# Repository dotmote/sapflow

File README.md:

# Sapflow Using the External Heat Ratio Method

So you want to measure sapflow in plants? You and me both, buddy. The goal of this project is to create an open-source, accurate, robust, low-cost, and low-power system to help answer the age-old question: "How is my plant doing?"

## Getting Started
Take a look at the hardware and software sections below for instructions on what you'll need to set up your own system and join in on improving the project.

## Hardware

### Sapflow Gauge
First, you'll need a way to measure and record the temperature at two specific points (equidistant from a central heating element) along the stem of your plant:

To build the gauge, you'll need: (1) the PCB; and (2) the components.

#### Fabricate the PCB
See here for the [KiCad PCB files](/hardware/sapflow_gauge/kicad/sapflow_gauge). Follow the directions from your favorite PCB fabrication service (e.g., OSHPark, JLCPCB, Seeed Studio, etc.), and order your desired quantity of PCBs.

#### Gather the Parts
See here for the [parts list](/hardware/sapflow_gauge/sapflow_gauge_parts.md). Go to your favorite electronic components distributor (e.g., Digikey, Arrow, Mouser, etc.) and order your desired quantity of components.

### Microcontroller
Second, you'll need a microcontroller that has an available GPIO pin (3.3V to 5V) and can communicate via I2C. We've found the ESP32 (specifically, the [LOLIN D32 Pro](https://www.aliexpress.com/item/32883116057.html) dev board) to be great for rapid prototyping with its relatively large onboard RAM, built-in WiFi, and low cost. For field experiments, it might make more sense to use a board with more low-power optimizations.

#### Microcontroller Shield
To reduce wiring, you might want to use a shield to interface your microcontroller with the sapflow gauge connector. See [here](/hardware/microcontroller_shield/d32_pro/d32_shield.md) for our shield design for the D32 Pro.

## Software

### Microcontroller Firmware
You'll need software running on your microcontroller to read data from the connected sapflow gauge. See [here](/software/microcontroller/d32_pro) for the Arduino code we used for the D32 Pro.

### Edge Compute Node
If you're using microcontrollers with WiFi connectivity, it's very convenient to have all of the data streaming into a single place. We like using a Raspberry Pi as an [MQTT](https://mosquitto.org/) broker, collecting data points from all of the networked sensor devices. See [here](/software/edge_compute_node/raspberry_pi) for more info.

## Data Visualization

Visualize your hard-earned data with this [Observable notebook](https://observablehq.com/d/a2d68ed97662840b).

Raw data:

After processing:

## References
We've stood on the shoulders of countless giants in working on this project. Below is a non-exhaustive list of the many previous efforts that we drew heavily from (let us know who we've missed and we'll make sure to add them):

### Sapflow
- Burgess, S.S.O., Adams, M.A., Turner, N.C., Beverly, C.R., Ong, C.K., Khan, A.A.H., and Bleby, T.M. (2001). An improved heat pulse method to measure low and reverse rates of sap flow in woody plants. Tree Physiology 21, 589–598. 
- Clearwater, M.J., Luo, Z., Mazzeo, M., and Dichio, B. (2009). An external heat pulse method for measurement of sap flow through fruit pedicels, leaf petioles and other small-diameter stems. Plant, Cell & Environment 32, 1652–1663.
- Marshall, D.C. (1958). Measurement of Sap Flow in Conifers by Heat Transport. Plant Physiol. 33, 385–396.
- Skelton, R. (2017). Miniature External Sapflow Gauges and the Heat Ratio Method for Quantifying Plant Water Loss. BIO-PROTOCOL 7.

### Open-Source Research Tools
- Chris Lucani & Team @ Brodribb Lab, University of Tasmania: [Open Source OV](http://www.opensourceov.org/).
- OPEnS Lab, Oregon State University: [Sap Flow Meter](https://github.com/OPEnSLab-OSU/OPEnS-Lab-Home/wiki/Sap-Flow-Meter).

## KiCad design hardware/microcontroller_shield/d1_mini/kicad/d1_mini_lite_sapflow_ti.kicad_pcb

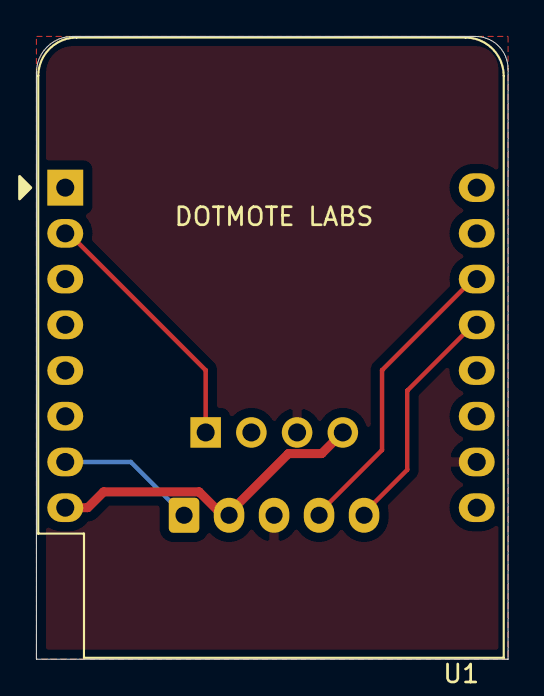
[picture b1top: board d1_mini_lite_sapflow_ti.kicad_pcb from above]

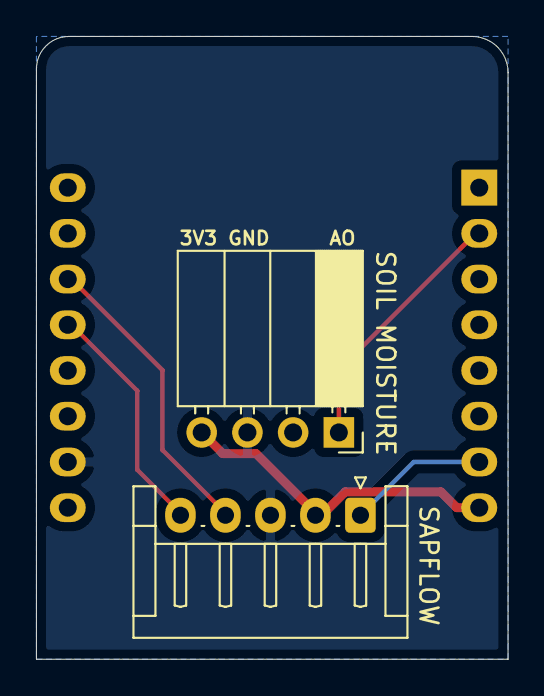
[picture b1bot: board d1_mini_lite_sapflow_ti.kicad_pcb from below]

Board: 2 copper layers, 26.2 x 34.6 mm, 3 parts (2 on the bottom side), 6 nets.

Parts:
SAPFLOW: sapflow_gauge_5_pin; JST_EH_S5B-EH_1x05_P2.50mm_Horizontal
SOIL MOISTURE: soil_moisture_4_pin; PinSocket_1x04_P2.54mm_Horizontal
U1: WeMos_D1_mini; WEMOS_D1_mini_light

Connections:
+3V3: SAPFLOW.2, SOIL MOISTURE.4, U1.8
GND: SAPFLOW.3, SOIL MOISTURE.3, U1.10
unnamed: SOIL MOISTURE.1, U1.2
unnamed: SAPFLOW.1, U1.7
unnamed: SAPFLOW.5, U1.13
unnamed: SAPFLOW.4, U1.14

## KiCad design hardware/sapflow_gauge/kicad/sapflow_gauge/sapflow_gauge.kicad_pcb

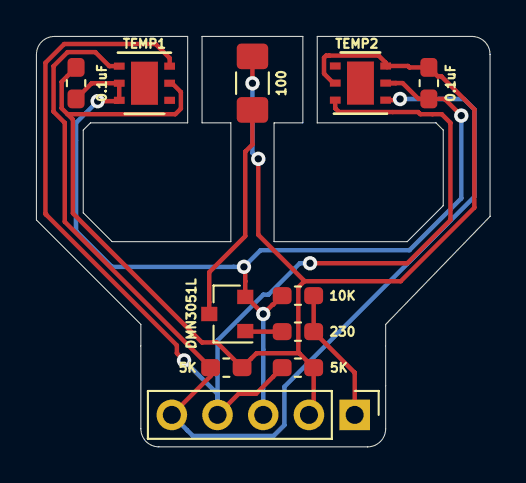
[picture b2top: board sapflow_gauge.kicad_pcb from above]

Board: 2 copper layers, 25.2 x 22.8 mm, 11 parts (0 on the bottom side), 7 nets.

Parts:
0.1uF, 0.1uF#2: 0.1uF; C_0603_1608Metric_Pad1.05x0.95mm_HandSolder
5K, 5K#2: 5K; R_0603_1608Metric_Pad1.05x0.95mm_HandSolder
10K: 10K; R_0603_1608Metric_Pad1.05x0.95mm_HandSolder
100: 100; R_1206_3216Metric_Pad1.42x1.75mm_HandSolder
230: 230; R_0603_1608Metric_Pad1.05x0.95mm_HandSolder
 : Conn_01x05_Female; PinHeader_1x05_P2.54mm_Vertical
DMN3051L: DMN3051L; SOT-23
TEMP1, TEMP2: HDC2080; Texas_PWSON-N6

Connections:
+3V3: 0.1uF.1, 0.1uF#2.1, 5K.1, 5K#2.1, 100.2, .2, TEMP1.5, TEMP2.3, TEMP2.5
GND: 0.1uF.2, 0.1uF#2.2, 10K.1, .3, DMN3051L.2, TEMP1.2, TEMP1.3, TEMP2.2
unnamed: 10K.2, 230.1, .1
unnamed: 5K.2, .4, TEMP1.6, TEMP2.6
unnamed: 5K#2.2, .5, TEMP1.1, TEMP2.1
unnamed: 230.2, DMN3051L.1
unnamed: 100.1, DMN3051L.3

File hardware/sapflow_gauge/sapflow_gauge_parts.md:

# Sapflow Gauge Parts

![sapflow gauge 3d](/docs/sapflow_gauge_3d.png)

In order to use the gauge, you'll need to:
1. Build the gauge head; and
2. Connect the gauge head to your microcontroller.

## Gauge Head Parts

Digikey links provided for convenience, but feel free to order from your favorite electronic components distributor.
| Part | Link | Quantity Needed Per Gauge |
|----------------------------------|------------------------------------------------------------------------------------------------------------------|---------------------------|
| HDC2080 Temperature & Humidity Sensor (6-WSON Package) | https://www.digikey.com/product-detail/en/texas-instruments/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 | 2 |
| DMN3051L-7 Logic Level Mosfet (SOT23 Package) | https://www.digikey.com/product-detail/en/diodes-incorporate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 | 1 |
| 100 Ohm Resistor (1206 Package) | https://www.digikey.com/product-detail/en/stackpole-electron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 | 1 |
| 270 Ohm Resistor (0603 Package) | https://www.digikey.com/product-detail/en/panasonic-electron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 | 1 |
| 5K Ohm Resistor (0603 Package) | https://www.digikey.com/product-detail/en/te-connectivity-pa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 | 2 |
| 10K Ohm Resistor (0603 Package) | https://www.digikey.com/product-detail/en/stackpole-electron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 | 1 |
| 0.1 uF Capacitor (0603 Package) | https://www.digikey.com/product-detail/en/samsung-electro-me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 | 2 |

## Gauge Head Connector Parts
You can use any method you'd like to connect the 5 pins (HEAT, 3V3, GND, SCL, SDA) from the gauge head to your microcontroller. We've had good results using RJ11 connectors with CAT3 ethernet cables up to ~10 feet (~3 meters).

| Part | Link |
|-----------------------|-------------------------------------------------------------------------------------------------|
| RJ11 Breakout Board | https://www.digikey.com/product-detail/en/sparkfun-electroni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 |
| RJ11 Female Connector | https://www.digikey.com/product-detail/en/amphenol-icc-fci/5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 |

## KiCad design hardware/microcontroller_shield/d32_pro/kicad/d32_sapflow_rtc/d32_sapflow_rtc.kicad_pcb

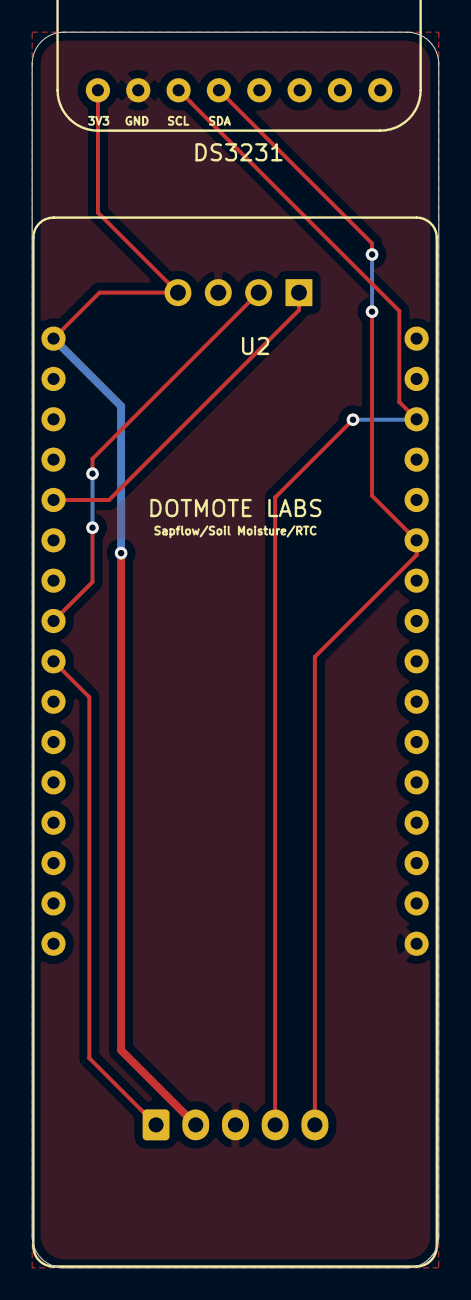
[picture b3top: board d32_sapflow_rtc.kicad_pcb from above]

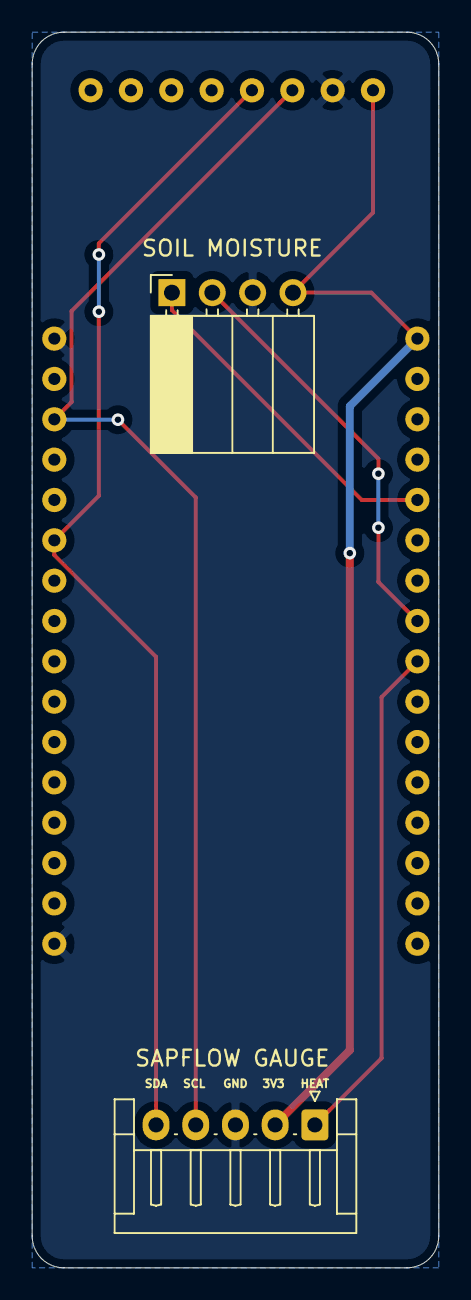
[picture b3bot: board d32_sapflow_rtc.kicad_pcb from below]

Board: 2 copper layers, 25.6 x 77.8 mm, 4 parts (2 on the bottom side), 7 nets.

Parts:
SAPFLOW GAUGE: sapflow_gauge_5_pin; JST_EH_S5B-EH_1x05_P2.50mm_Horizontal
SOIL MOISTURE: soil_moisture_4_pin; PinSocket_1x04_P2.54mm_Horizontal
U2: d32_pro
U4: adafruit_ds3231

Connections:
+3V3: SAPFLOW GAUGE.2, SOIL MOISTURE.4, U2.1, U4.1
GND: SAPFLOW GAUGE.3, SOIL MOISTURE.3, U2.17, U2.32, U4.2
unnamed: SOIL MOISTURE.1, U2.5
unnamed: SOIL MOISTURE.2, U2.8
unnamed: SAPFLOW GAUGE.1, U2.9
unnamed: SAPFLOW GAUGE.5, U2.27, U4.4
unnamed: SAPFLOW GAUGE.4, U2.30, U4.3

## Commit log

2019-12-27 initial release
2019-12-29 fix copy
2019-12-29 add build steps for gauge
2020-01-02 add hdc2080 library dependency
2020-01-24 add gerbers for sapflow gauge; update silkscreen
2020-01-24 add esp32 arduino IDE boards manager URL
2020-01-28 add d1 mini arduino code
2020-02-04 enable logging of mqtt messages
2020-02-04 add instructions for creating a data directory in the raspberry pi
2020-02-04 fix rtcUnixTimestamp offset
2020-02-07 note required adjustment for rtcUnixTimestamp value
2020-02-10 add d1 mini shield
2020-02-17 add csv aggregator script for merging CSVs
2020-02-17 Analysis in R to run some sanity checks
2020-02-17 add human readable timestamp for raspberry pi receiving mqtt datapoints
2020-02-28 Heat-ratio-validation script
2020-03-23 add d32 firmware without RTC code
2020-03-24 initial commit of mqtt_web_server
2020-03-25 use npm instead of yarn for react
2020-03-25 functional prototype of web server dashboard
2020-03-25 swap useState for useReducer
2020-03-26 update dependency
2020-03-26 add heartbeat mechanism to report node status; swap useReducer for useState
2020-03-26 add mqtt device simulator
2020-03-26 refactor timeReceived
2020-03-26 remove logging
2020-03-27 fix device simulator logic
2020-03-28 update title
2020-03-28 implement websockets
2020-03-28 fix data generator
2020-03-28 add readme
2020-03-28 implement mDNS
2020-03-28 update favicon
2020-03-29 refactor mqtt device simulator; add logging
2020-03-29 update dependencies
2020-04-03 move README to correct folder
2020-04-05 add heat ratio processing script
2020-04-08 implement periodic file upload
2020-04-20 use cron npm package to schedule uploads
2020-05-06 track build directory
2020-05-08 remove last modified check for uploading files
2020-05-17 change client id in mqtt_web_server for mqtt subscription
2020-07-19 Bump lodash in /software/data_analysis/csvAggregator
    Bumps [lodash](https://github.com/lodash/lodash) from 4.17.15 to 4.17.19.
    - [Release notes](https://github.com/lodash/lodash/releases)
    - [Commits](https://github.com/lodash/lodash/compare/4.17.15...4.17.19)
2020-12-08 Bump fast-csv in /software/edge_compute_node/raspberry_pi/mqtt_nodejs
    Bumps [fast-csv](https://github.com/C2FO/fast-csv/tree/HEAD/packages/fast-csv) from 2.5.0 to 4.3.6.
    - [Release notes](https://github.com/C2FO/fast-csv/releases)
    - [Changelog](https://github.com/C2FO/fast-csv/blob/master/packages/fast-csv/CHANGELOG.md)
    - [Commits](https://github.com/C2FO/fast-csv/commits/v4.3.6/packages/fast-csv)
2020-12-08 Bump fast-csv
    Bumps [fast-csv](https://github.com/C2FO/fast-csv/tree/HEAD/packages/fast-csv) from 2.5.0 to 4.3.6.
    - [Release notes](https://github.com/C2FO/fast-csv/releases)
    - [Changelog](https://github.com/C2FO/fast-csv/blob/master/packages/fast-csv/CHANGELOG.md)
    - [Commits](https://github.com/C2FO/fast-csv/commits/v4.3.6/packages/fast-csv)
2020-12-16 Introductory Notebook explaining sapflow analysis
2020-12-16 Data files for four nodes
2020-12-16 Bump bl
    Bumps [bl](https://github.com/rvagg/bl) from 1.2.2 to 1.2.3.
    - [Release notes](https://github.com/rvagg/bl/releases)
    - [Commits](https://github.com/rvagg/bl/compare/v1.2.2...v1.2.3)
2020-12-16 Bump bl in /software/edge_compute_node/raspberry_pi/mqtt_nodejs
    Bumps [bl](https://github.com/rvagg/bl) from 1.2.2 to 1.2.3.
    - [Release notes](https://github.com/rvagg/bl/releases)
    - [Commits](https://github.com/rvagg/bl/compare/v1.2.2...v1.2.3)
2021-01-02 Revision
2021-02-09 Test the ET ~SV relationship
2021-02-12 Data for Seattle ET
2021-05-03 Gravi with analysis
2021-05-03 data
2021-05-03 figs and update
2021-05-11 Bump lodash in /software/data_analysis/csvAggregator
    Bumps [lodash](https://github.com/lodash/lodash) from 4.17.19 to 4.17.21.
    - [Release notes](https://github.com/lodash/lodash/releases)
    - [Commits](https://github.com/lodash/lodash/compare/4.17.19...4.17.21)
2021-05-13 updae
2021-05-17 Update with correlation
2021-05-17 Fixed the figure
2021-05-17 Test the checkin
2021-05-21 Comparison of flows
2021-05-21 Sapflow compare
2021-05-30 Bump ws
    Bumps [ws](https://github.com/websockets/ws) from 7.2.3 to 7.4.6.
    - [Release notes](https://github.com/websockets/ws/releases)
    - [Commits](https://github.com/websockets/ws/compare/7.2.3...7.4.6)
2021-06-11 Bump normalize-url
    Bumps [normalize-url](https://github.com/sindresorhus/normalize-url) from 4.5.0 to 4.5.1.
    - [Release notes](https://github.com/sindresorhus/normalize-url/releases)
    - [Commits](https://github.com/sindresorhus/normalize-url/commits)
    ---
    updated-dependencies:
    - dependency-name: normalize-url
2022-03-25 Bump minimist in /software/edge_compute_node/raspberry_pi/mqtt_nodejs
    Bumps [minimist](https://github.com/substack/minimist) from 1.2.5 to 1.2.6.
    - [Release notes](https://github.com/substack/minimist/releases)
    - [Commits](https://github.com/substack/minimist/compare/1.2.5...1.2.6)
    ---
    updated-dependencies:
    - dependency-name: minimist
2022-03-26 Bump minimist
    Bumps [minimist](https://github.com/substack/minimist) from 1.2.5 to 1.2.6.
    - [Release notes](https://github.com/substack/minimist/releases)
    - [Commits](https://github.com/substack/minimist/compare/1.2.5...1.2.6)
    ---
    updated-dependencies:
    - dependency-name: minimist
2022-03-26 Bump minimist in /software/data_analysis/processAndLogHeatRatioLocal
    Bumps [minimist](https://github.com/substack/minimist) from 1.2.5 to 1.2.6.
    - [Release notes](https://github.com/substack/minimist/releases)
    - [Commits](https://github.com/substack/minimist/compare/1.2.5...1.2.6)
    ---
    updated-dependencies:
    - dependency-name: minimist
2022-04-09 Bump moment
    Bumps [moment](https://github.com/moment/moment) from 2.24.0 to 2.29.2.
    - [Release notes](https://github.com/moment/moment/releases)
    - [Changelog](https://github.com/moment/moment/blob/develop/CHANGELOG.md)
    - [Commits](https://github.com/moment/moment/compare/2.24.0...2.29.2)
    ---
    updated-dependencies:
2022-06-22 Bump got
    Bumps [got](https://github.com/sindresorhus/got) from 10.7.0 to 11.8.5.
    - [Release notes](https://github.com/sindresorhus/got/releases)
    - [Commits](https://github.com/sindresorhus/got/compare/v10.7.0...v11.8.5)
    ---
    updated-dependencies:
    - dependency-name: got
2022-07-07 Bump moment
    Bumps [moment](https://github.com/moment/moment) from 2.24.0 to 2.29.4.
    - [Release notes](https://github.com/moment/moment/releases)
    - [Changelog](https://github.com/moment/moment/blob/develop/CHANGELOG.md)
    - [Commits](https://github.com/moment/moment/compare/2.24.0...2.29.4)
    ---
    updated-dependencies:
2022-08-31 Bump moment-timezone
    Bumps [moment-timezone](https://github.com/moment/moment-timezone) from 0.5.28 to 0.5.37.
    - [Release notes](https://github.com/moment/moment-timezone/releases)
    - [Changelog](https://github.com/moment/moment-timezone/blob/develop/changelog.md)
    - [Commits](https://github.com/moment/moment-timezone/compare/0.5.28...0.5.37)
    ---
    updated-dependencies:
2022-12-07 Bump qs and express
    Bumps [qs](https://github.com/ljharb/qs) to 6.11.0 and updates ancestor dependency [express](https://github.com/expressjs/express). These dependencies need to be updated together.
    Updates `qs` from 6.7.0 to 6.11.0
    - [Release notes](https://github.com/ljharb/qs/releases)
    - [Changelog](https://github.com/ljharb/qs/blob/main/CHANGELOG.md)
    - [Commits](https://github.com/ljharb/qs/compare/v6.7.0...v6.11.0)
    Updates `express` from 4.17.1 to 4.18.2
2022-12-12 Bump express
    Bumps [express](https://github.com/expressjs/express) from 4.17.1 to 4.17.3.
    - [Release notes](https://github.com/expressjs/express/releases)
    - [Changelog](https://github.com/expressjs/express/blob/master/History.md)
    - [Commits](https://github.com/expressjs/express/compare/4.17.1...4.17.3)
    ---
    updated-dependencies:
2023-09-13 updsate
